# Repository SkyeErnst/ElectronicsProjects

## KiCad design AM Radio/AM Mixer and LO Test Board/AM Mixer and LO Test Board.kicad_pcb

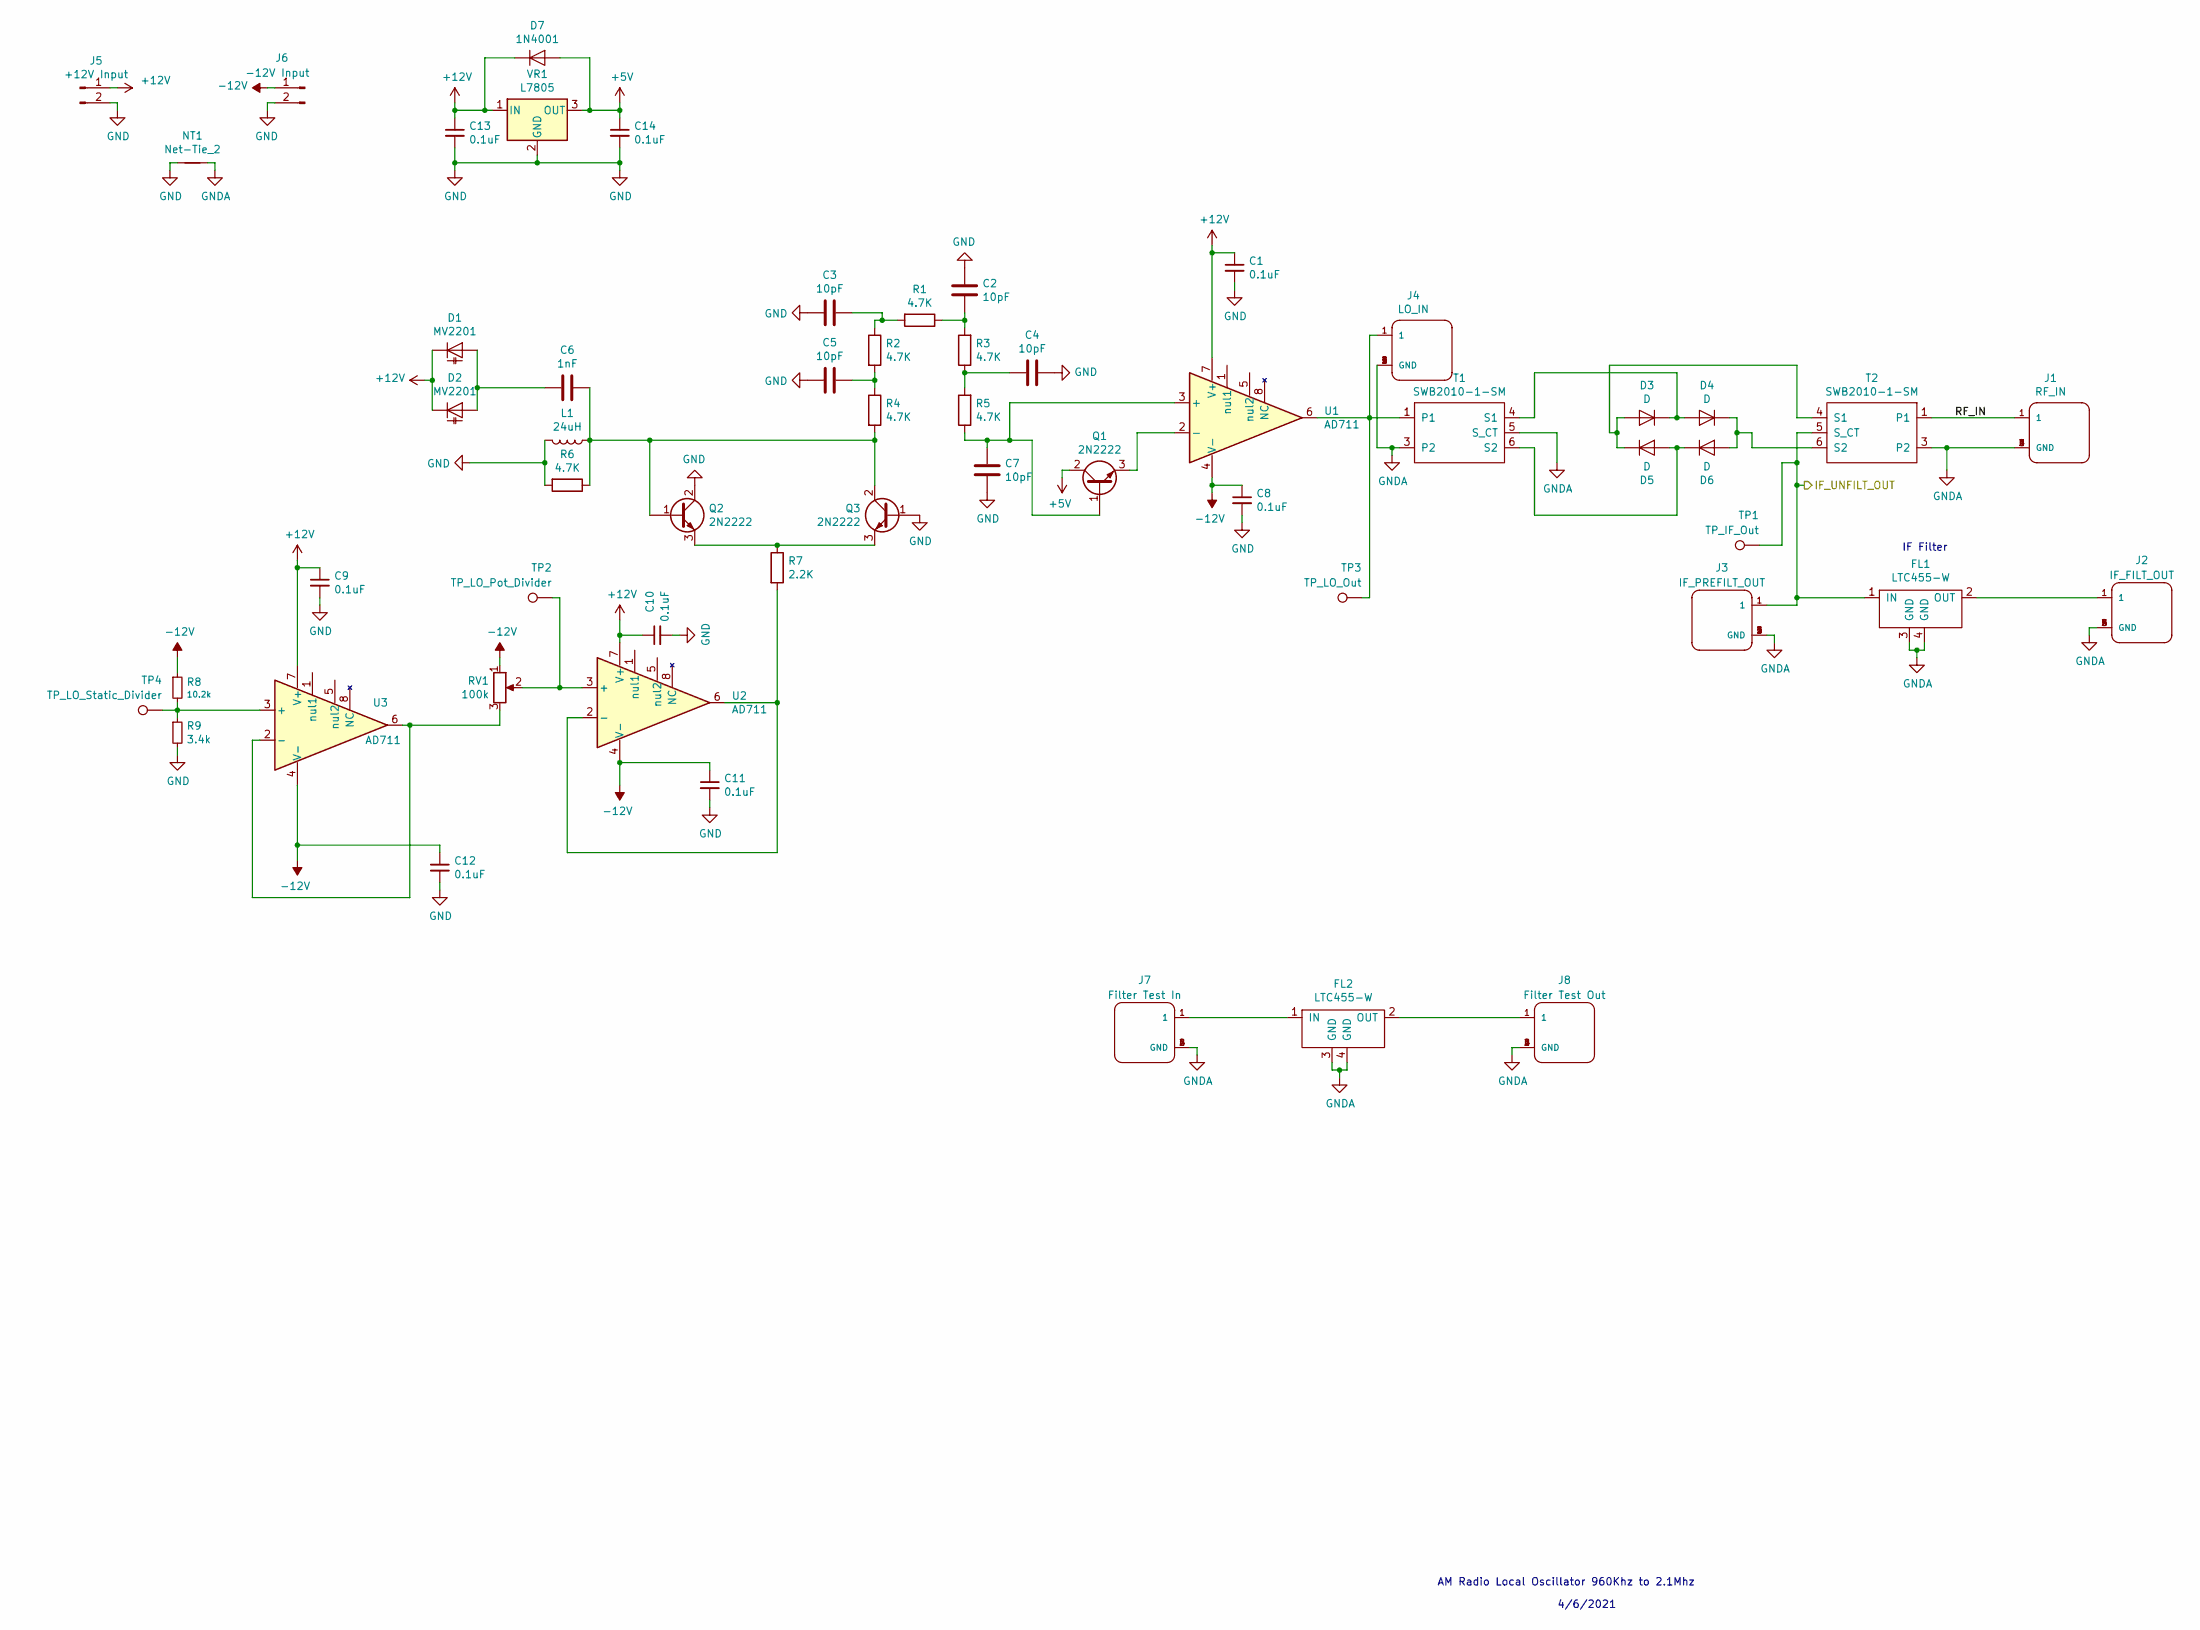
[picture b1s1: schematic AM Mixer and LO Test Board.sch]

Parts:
C1, C8, C9, C10, C11, C12, C13, C14: 0.1uF; C_0805_2012Metric_Pad1.15x1.40mm_HandSolder
C2, C3, C4, C5, C7: 10pF; C_Disc_D3.8mm_W2.6mm_P2.50mm
C6: 1nF; C_Disc_D3.8mm_W2.6mm_P2.50mm
D1, D2: MV2201; C_0402_1005Metric
D3, D4, D5, D6: D; _SC79
D7: 1N4001; D_DO-15_P15.24mm_Horizontal
FL1, FL2: LTC455-W
J1: RF_IN; TE_5-1634503-1
J2: IF_FILT_OUT; TE_5-1634503-1
J3: IF_PREFILT_OUT; TE_5-1634503-1
J4: LO_IN; TE_5-1634503-1
J5: +12V Input; PinHeader_1x02_P2.54mm_Vertical
J6: -12V Input; PinHeader_1x02_P2.54mm_Vertical
J7: Filter Test In; TE_5-1634503-1
J8: Filter Test Out; TE_5-1634503-1
L1: 24uH; L_Axial_L24.0mm_D7.1mm_P30.48mm_Horizontal_Vishay_IM-10-28
NT1: Net-Tie_2; NetTie-2_SMD_Pad0.5mm
Q1, Q2, Q3: 2N2222; TO-92L_HandSolder
R1, R2, R3, R4, R5, R6: 4.7K; R_Axial_DIN0411_L9.9mm_D3.6mm_P15.24mm_Horizontal
R7: 2.2K; R_Axial_DIN0411_L9.9mm_D3.6mm_P15.24mm_Horizontal
R8: 10.2k; R_Axial_DIN0411_L9.9mm_D3.6mm_P15.24mm_Horizontal
R9: 3.4k; R_Axial_DIN0411_L9.9mm_D3.6mm_P15.24mm_Horizontal
RV1: 100k; PinHeader_1x03_P2.54mm_Vertical
T1, T2: SWB2010-1-SM
TP1: TP_IF_Out; TestPoint_Pad_2.5x2.5mm
TP2: TP_LO_Pot_Divider; TestPoint_Pad_2.5x2.5mm
TP3: TP_LO_Out; TestPoint_Pad_2.5x2.5mm
TP4: TP_LO_Static_Divider; TestPoint_Pad_2.5x2.5mm
U1, U2, U3: AD711; DIP-8_W7.62mm_LongPads
VR1: L7805; TO-220-3_Vertical

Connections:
+5V: C14.1, D7.2 (A), Q1.2 (C), VR1.3 (OUT)
+12V: C1.1, C9.1, C10.1, C13.1, D1.1 (K), D2.1 (K), D7.1 (K), J5.1, U1.7 (V+), U2.7 (V+), U3.7 (V+), VR1.1 (IN)
-12V: C8.1, C11.1, C12.1, J6.1, R8.1, RV1.1, U1.4 (V-), U2.4 (V-), U3.4 (V-)
/IF_UNFILT_OUT: FL1.1 (IN), J3.1, T2.5 (S_CT), TP1.1
/RF_IN: J1.1, T2.1
GND: C1.2, C2.1, C3.1, C4.1, C5.1, C7.1, C8.2, C9.2, C10.2, C11.2, C12.2, C13.2, C14.2, J5.2, J6.2, L1.2, NT1.1, Q2.2 (C), Q3.1 (B), R6.2, R9.2, VR1.2 (GND)
GNDA: FL1.3 (GND), FL1.4 (GND), FL2.3 (GND), FL2.4 (GND), J1.2 (GND), J1.3 (GND), J1.4 (GND), J1.5 (GND), J2.2 (GND), J2.3 (GND), J2.4 (GND), J2.5 (GND), J3.2 (GND), J3.3 (GND), J3.4 (GND), J3.5 (GND), J4.2 (GND), J4.3 (GND), J4.4 (GND), J4.5 (GND), J7.2 (GND), J7.3 (GND), J7.4 (GND), J7.5 (GND), J8.2 (GND), J8.3 (GND), J8.4 (GND), J8.5 (GND), NT1.2, T1.3 (P2), T1.5 (S_CT), T2.3 (P2)
unnamed: C2.2, R1.1, R3.2
unnamed: C3.2, R1.2, R2.1
unnamed: C4.2, R3.1, R5.2
unnamed: C5.2, R2.2, R4.1
unnamed: C6.1, L1.1, Q2.1 (B), Q3.2 (C), R4.2, R6.1
unnamed: C6.2, D1.2 (A), D2.2 (A)
unnamed: C7.2, Q1.1 (B), R5.1, U1.3 (+)
unnamed: D3.1 (K), D4.2 (A), T1.4 (S1)
unnamed: D3.2 (A), D5.1 (K), T2.4 (S1)
unnamed: D4.1 (K), D6.2 (A), T2.6 (S2)
unnamed: D5.2 (A), D6.1 (K), T1.6 (S2)
unnamed: FL1.2 (OUT), J2.1
unnamed: FL2.1 (IN), J7.1
unnamed: FL2.2 (OUT), J8.1
unnamed: J4.1, T1.1, TP3.1, U1.6
unnamed: Q1.3 (E), U1.2 (-)
unnamed: Q2.3 (E), Q3.3 (E), R7.1
unnamed: R7.2, U2.2 (-), U2.6
unnamed: R8.2, R9.1, TP4.1, U3.3 (+)
unnamed: RV1.2, TP2.1, U2.3 (+)
unnamed: RV1.3, U3.2 (-), U3.6

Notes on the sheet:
AM Radio Local Oscillator 960Khz to 2.1Mhz
4/6/2021
IF Filter

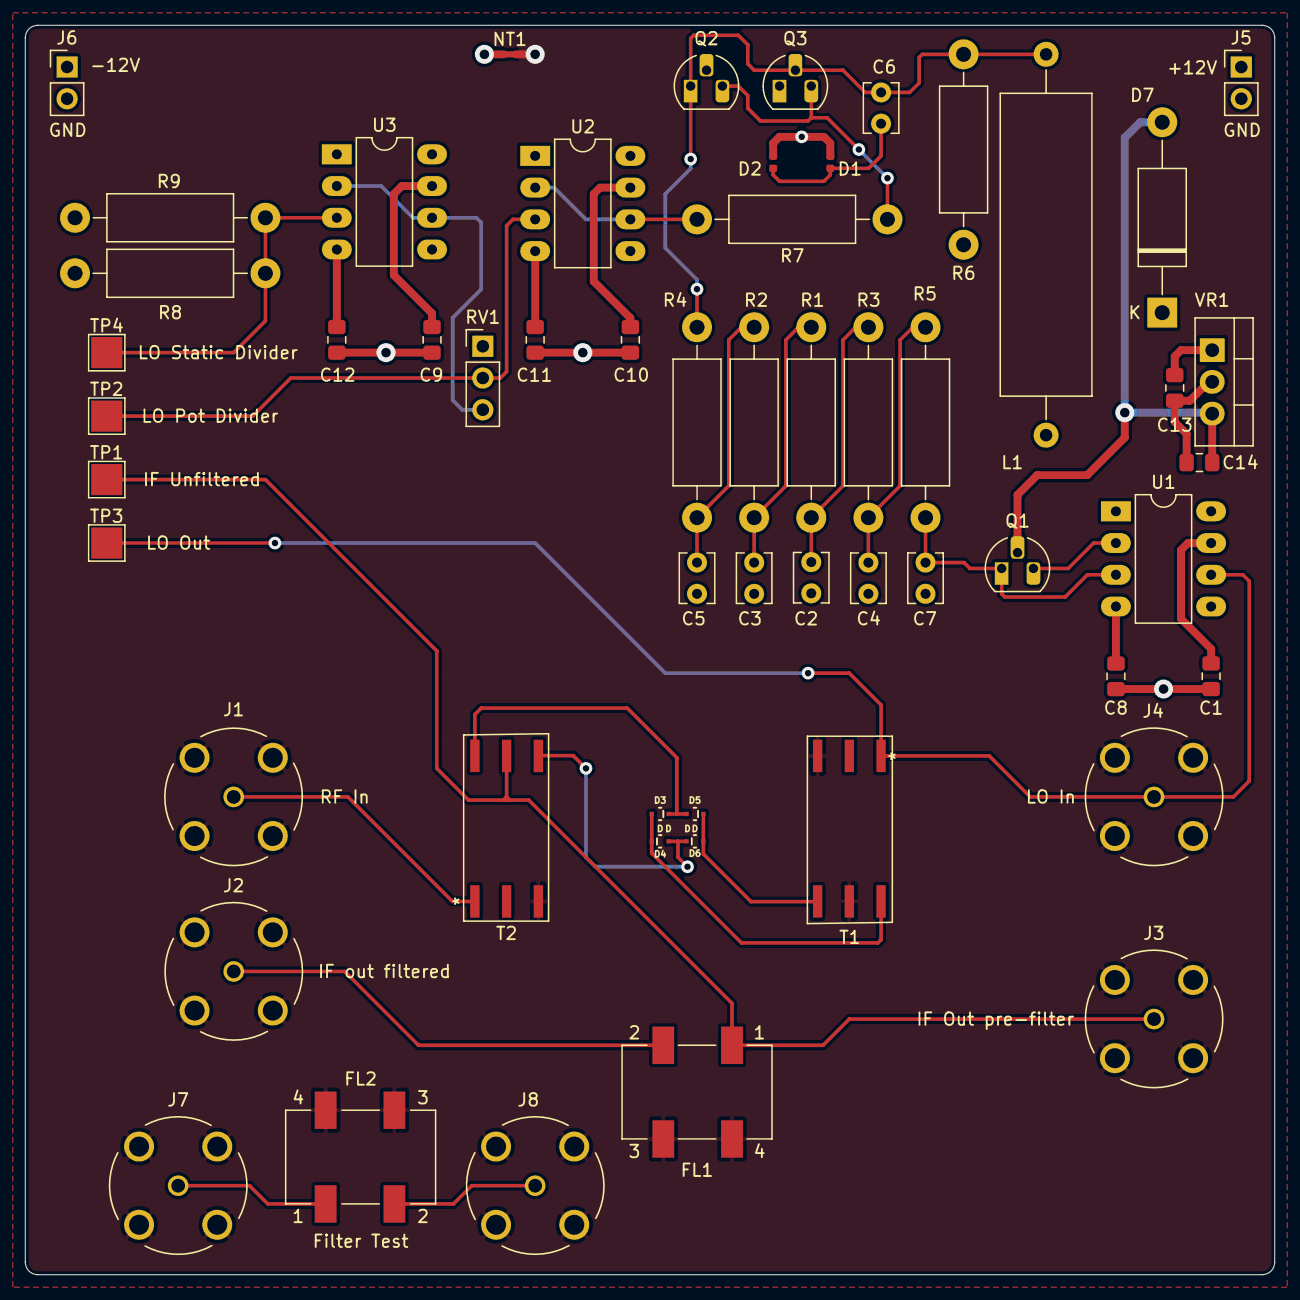
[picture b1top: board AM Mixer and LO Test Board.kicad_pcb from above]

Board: 4 copper layers, 100.0 x 100.0 mm, 56 parts (0 on the bottom side), 28 nets.

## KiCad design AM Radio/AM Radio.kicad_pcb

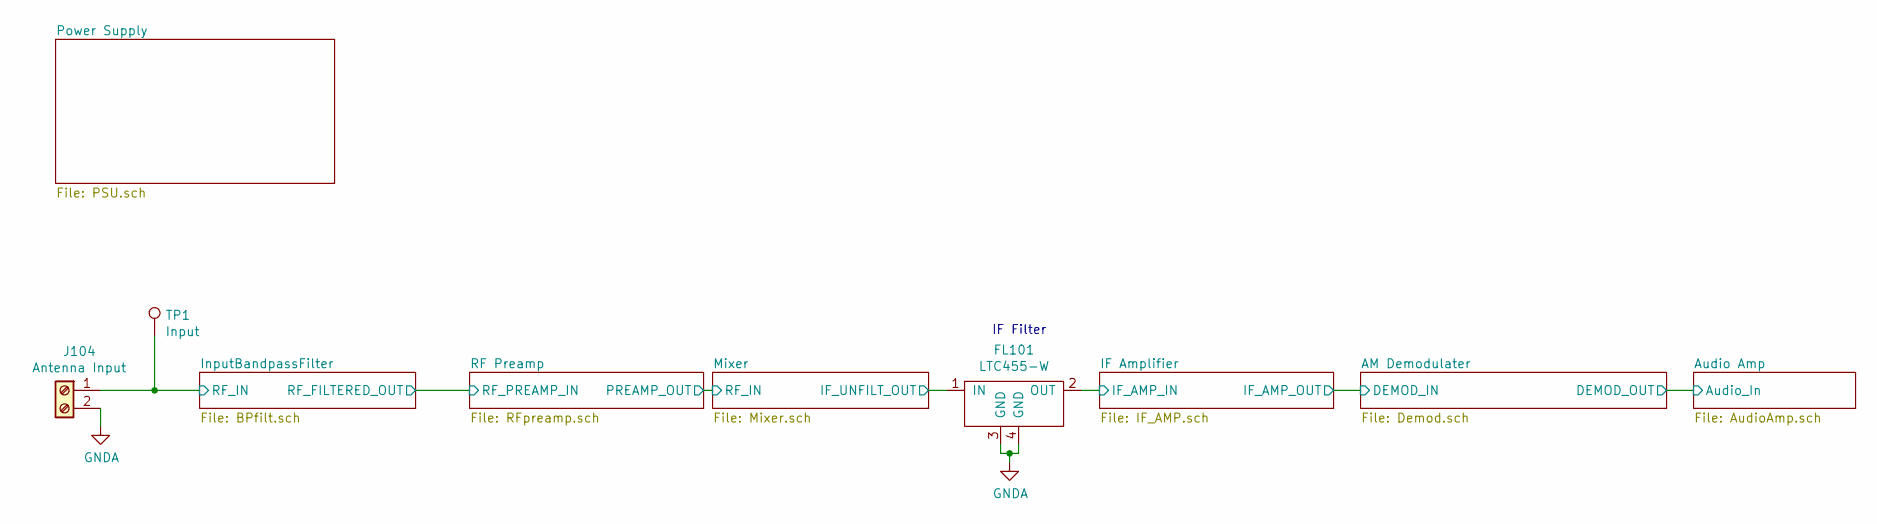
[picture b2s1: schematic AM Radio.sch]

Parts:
FL101: LTC455-W
J104: Antenna Input; Altech_AK300_1x02_P5.00mm_45-Degree
TP1: Input; TestPoint_Pad_2.5x2.5mm

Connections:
/IF Amplifier/IF_AMP_IN: FL101.2 (OUT); also elsewhere on the board
/InputBandpassFilter/RF_IN: J104.1, TP1.1; also elsewhere on the board
/Mixer/IF_UNFILT_OUT: FL101.1 (IN); also elsewhere on the board
GNDA: FL101.3 (GND), FL101.4 (GND), J104.2; also elsewhere on the board

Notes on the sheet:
IF Filter

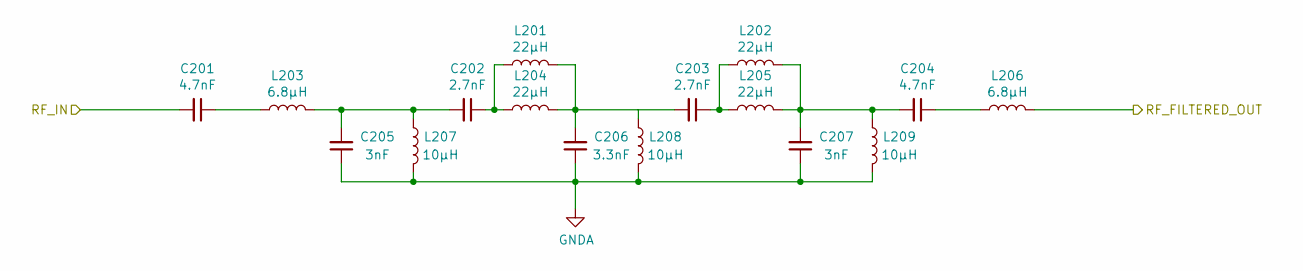
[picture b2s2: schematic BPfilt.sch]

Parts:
C201, C204: 4.7nF; C_0805_2012Metric_Pad1.15x1.40mm_HandSolder
C202, C203: 2.7nF; C_0805_2012Metric_Pad1.15x1.40mm_HandSolder
C205, C207: 3nF; C_0805_2012Metric_Pad1.15x1.40mm_HandSolder
C206: 3.3nF; C_0805_2012Metric_Pad1.15x1.40mm_HandSolder
L201, L202, L204, L205: 22µH; L_0805_2012Metric_Pad1.15x1.40mm_HandSolder
L203, L206: 6.8µH; L_0805_2012Metric_Pad1.15x1.40mm_HandSolder
L207, L208, L209: 10µH; L_0805_2012Metric_Pad1.15x1.40mm_HandSolder

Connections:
/InputBandpassFilter/RF_FILTERED_OUT: L206.2; also elsewhere on the board
/InputBandpassFilter/RF_IN: C201.2; also elsewhere on the board
GNDA: C205.1, C206.1, C207.1, L207.2, L208.2, L209.2; also elsewhere on the board
unnamed: C201.1, L203.1
unnamed: C202.1, L201.1, L204.1
unnamed: C202.2, C205.2, L203.2, L207.1
unnamed: C203.1, L202.1, L205.1
unnamed: C203.2, C206.2, L201.2, L204.2, L208.1
unnamed: C204.1, L206.1
unnamed: C204.2, C207.2, L202.2, L205.2, L209.1

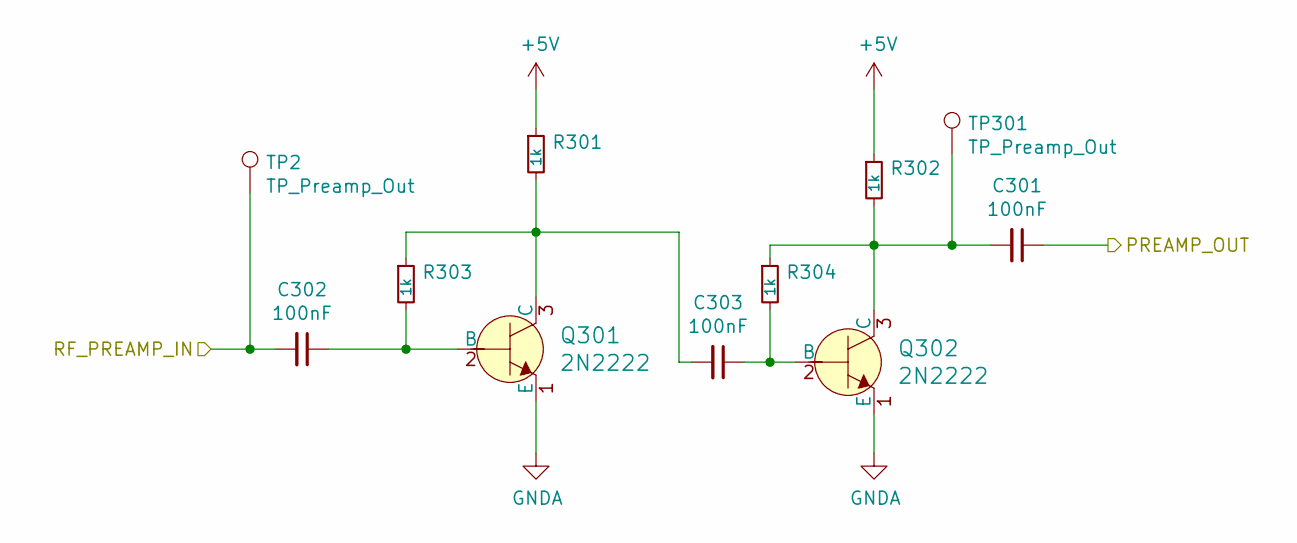
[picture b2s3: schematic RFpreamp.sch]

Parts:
C301, C302, C303: 100nF; C_0805_2012Metric_Pad1.15x1.40mm_HandSolder
Q301, Q302: 2N2222; SOT-23
R301, R302, R303, R304: 1k; R_0805_2012Metric_Pad1.15x1.40mm_HandSolder
TP2, TP301: TP_Preamp_Out; TestPoint_Pad_2.5x2.5mm

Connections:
+5V: R301.1, R302.1; also elsewhere on the board
/InputBandpassFilter/RF_FILTERED_OUT: C302.2, TP2.1; also elsewhere on the board
/RF Preamp/PREAMP_OUT: C301.1; also elsewhere on the board
GNDA: Q301.1 (E), Q302.1 (E); also elsewhere on the board
unnamed: C301.2, Q302.3 (C), R302.2, R304.1, TP301.1
unnamed: C302.1, Q301.2 (B), R303.2
unnamed: C303.1, Q302.2 (B), R304.2
unnamed: C303.2, Q301.3 (C), R301.2, R303.1

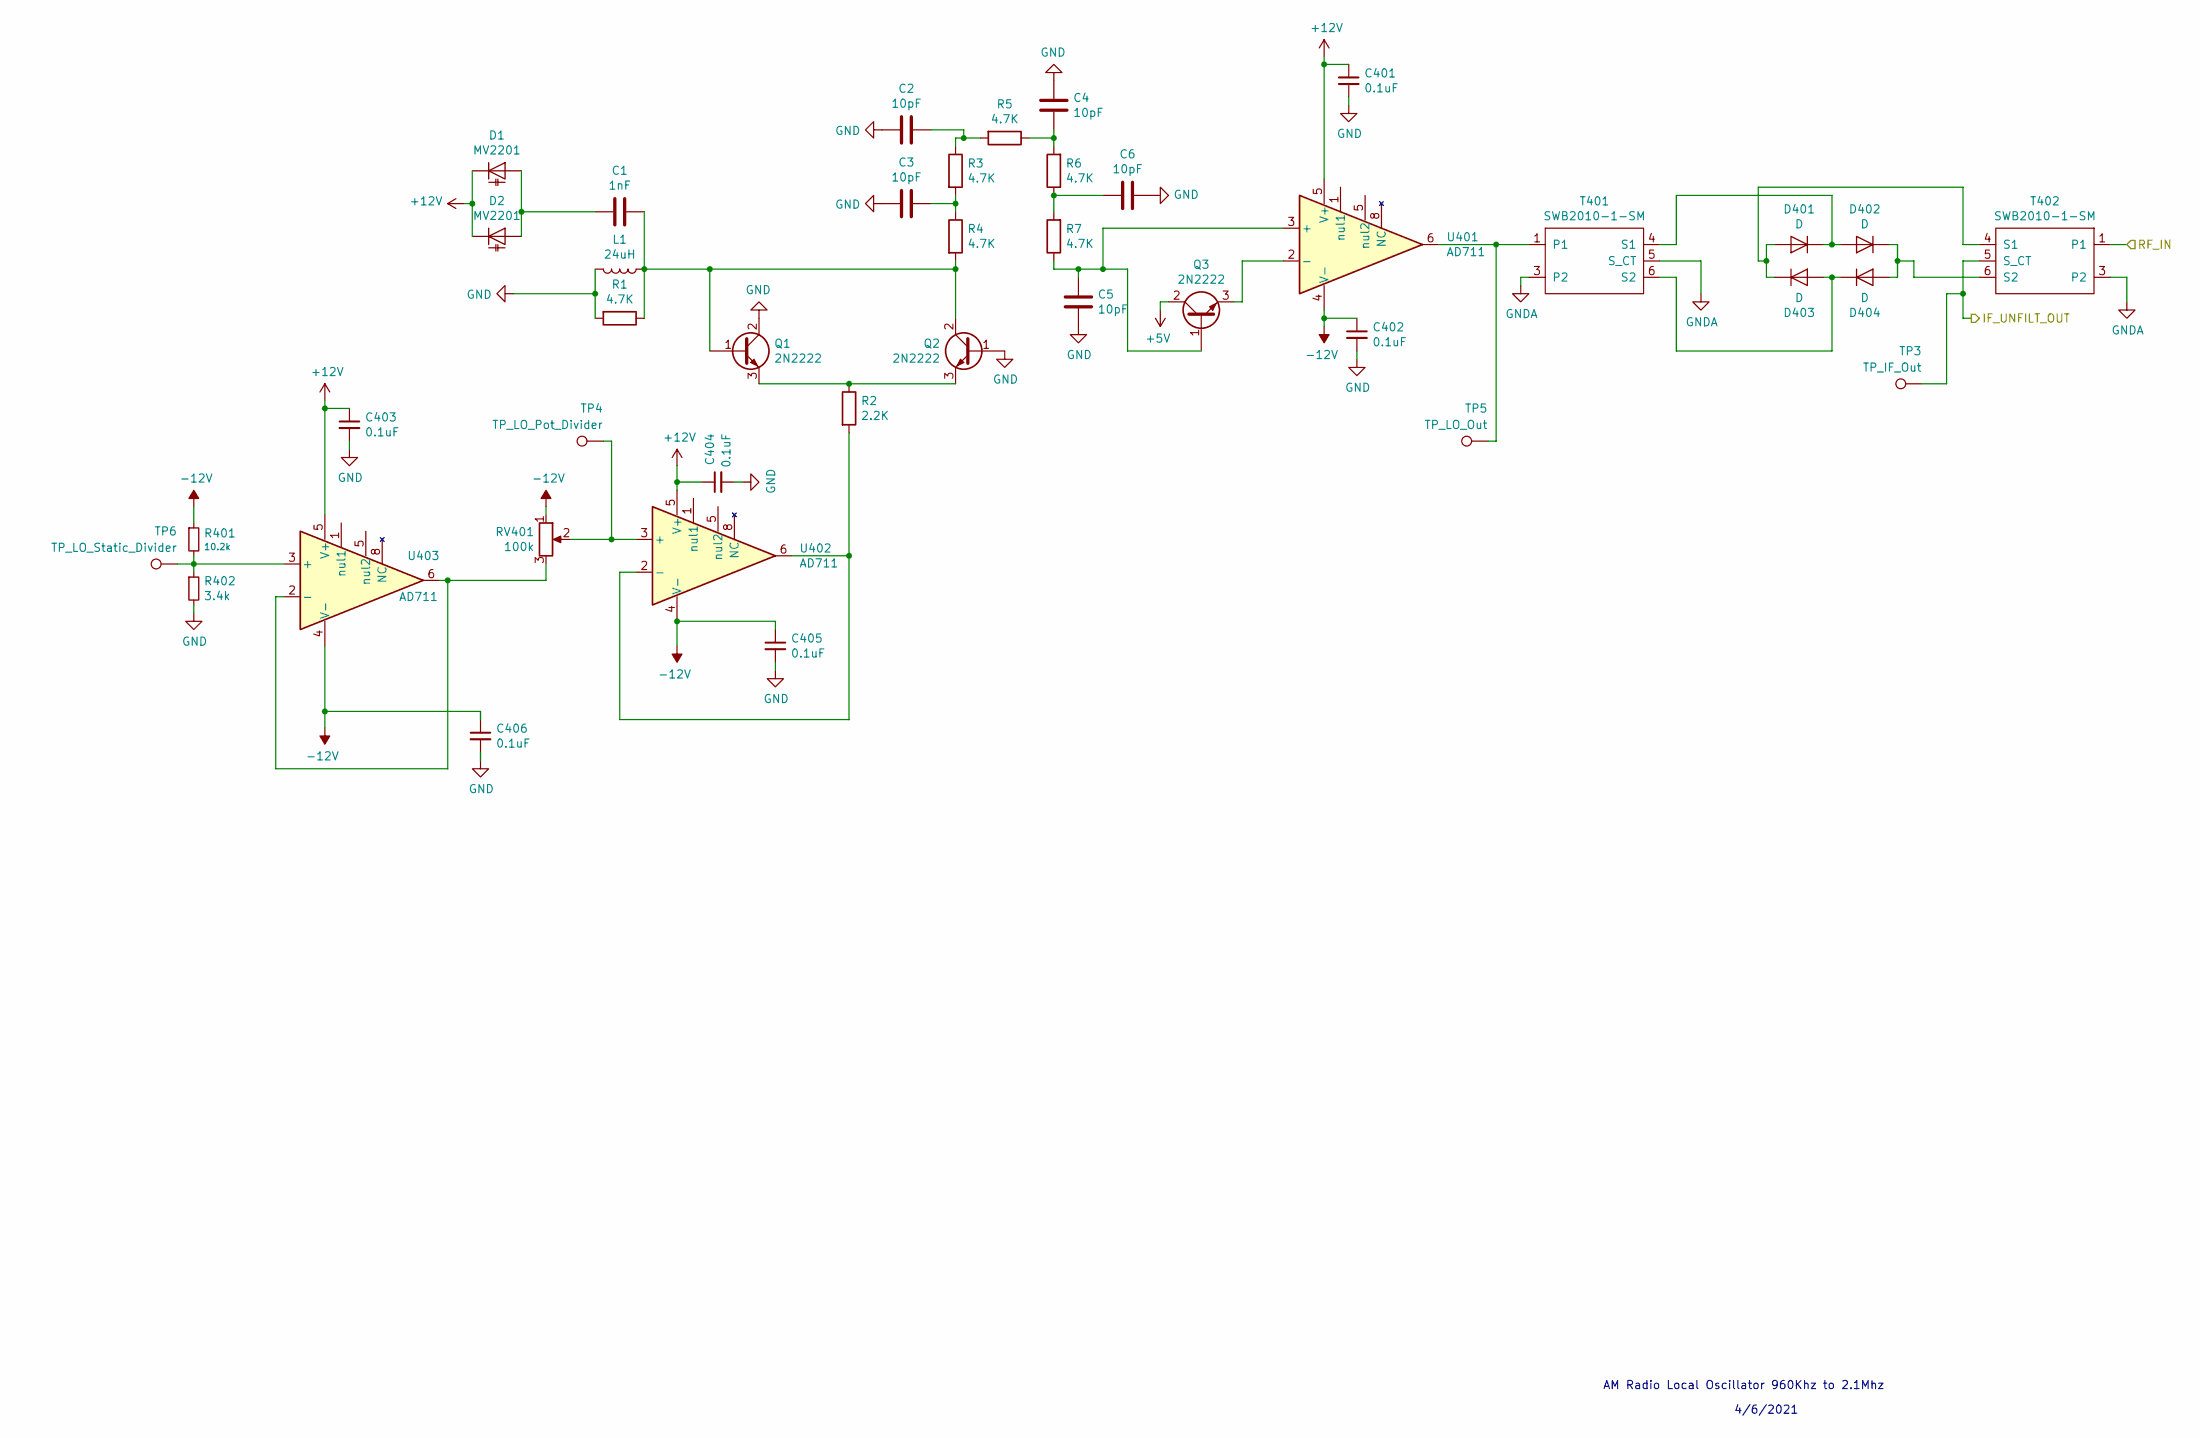
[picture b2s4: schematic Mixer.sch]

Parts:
C1: 1nF; C_0805_2012Metric_Pad1.15x1.40mm_HandSolder
C2, C3, C4, C5, C6: 10pF; C_0805_2012Metric_Pad1.15x1.40mm_HandSolder
C401, C402, C403, C404, C405, C406: 0.1uF; C_0805_2012Metric_Pad1.15x1.40mm_HandSolder
D1, D2: MV2201; C_0402_1005Metric
D401, D402, D403, D404: D; D_0805_2012Metric_Pad1.15x1.40mm_HandSolder
L1: 24uH; L_0805_2012Metric_Pad1.15x1.40mm_HandSolder
Q1, Q2, Q3: 2N2222; SOT-23
R1, R3, R4, R5, R6, R7: 4.7K; R_0805_2012Metric_Pad1.15x1.40mm_HandSolder
R2: 2.2K; R_0805_2012Metric_Pad1.15x1.40mm_HandSolder
R401: 10.2k; R_0805_2012Metric_Pad1.15x1.40mm_HandSolder
R402: 3.4k; R_0805_2012Metric_Pad1.15x1.40mm_HandSolder
RV401: 100k; Potentiometer_Bourns_3266W_Vertical
T401, T402: SWB2010-1-SM
TP3: TP_IF_Out; TestPoint_Pad_2.5x2.5mm
TP4: TP_LO_Pot_Divider; TestPoint_Pad_2.5x2.5mm
TP5: TP_LO_Out; TestPoint_Pad_2.5x2.5mm
TP6: TP_LO_Static_Divider; TestPoint_Pad_2.5x2.5mm
U401, U402, U403: AD711; DIP-8_W7.62mm_LongPads

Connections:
+5V: Q3.2 (C); also elsewhere on the board
+12V: C401.1, C403.1, C404.1, D1.1 (K), D2.1 (K), U401.5 (nul2), U402.5 (nul2), U403.5 (nul2); also elsewhere on the board
-12V: C402.1, C405.1, C406.1, R401.1, RV401.1, U401.4 (V-), U402.4 (V-), U403.4 (V-); also elsewhere on the board
/Mixer/IF_UNFILT_OUT: T402.5 (S_CT), TP3.1; also elsewhere on the board
/RF Preamp/PREAMP_OUT: T402.1; also elsewhere on the board
GND: C2.1, C3.1, C4.1, C5.1, C6.1, C401.2, C402.2, C403.2, C404.2, C405.2, C406.2, L1.2, Q1.2 (C), Q2.1 (B), R1.2, R402.2; also elsewhere on the board
GNDA: T401.3 (P2), T401.5 (S_CT), T402.3 (P2); also elsewhere on the board
unnamed: C1.1, L1.1, Q1.1 (B), Q2.2 (C), R1.1, R4.2
unnamed: C1.2, D1.2 (A), D2.2 (A)
unnamed: C2.2, R3.1, R5.2
unnamed: C3.2, R3.2, R4.1
unnamed: C4.2, R5.1, R6.2
unnamed: C5.2, Q3.1 (B), R7.1, U401.3 (+)
unnamed: C6.2, R6.1, R7.2
unnamed: D401.1 (K), D402.2 (A), T401.4 (S1)
unnamed: D401.2 (A), D403.1 (K), T402.4 (S1)
unnamed: D402.1 (K), D404.2 (A), T402.6 (S2)
unnamed: D403.2 (A), D404.1 (K), T401.6 (S2)
unnamed: Q1.3 (E), Q2.3 (E), R2.1
unnamed: Q3.3 (E), U401.2 (-)
unnamed: R2.2, U402.2 (-), U402.6
unnamed: R401.2, R402.1, TP6.1, U403.3 (+)
unnamed: RV401.2, TP4.1, U402.3 (+)
unnamed: RV401.3, U403.2 (-), U403.6
unnamed: T401.1, TP5.1, U401.6

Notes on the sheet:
AM Radio Local Oscillator 960Khz to 2.1Mhz
4/6/2021

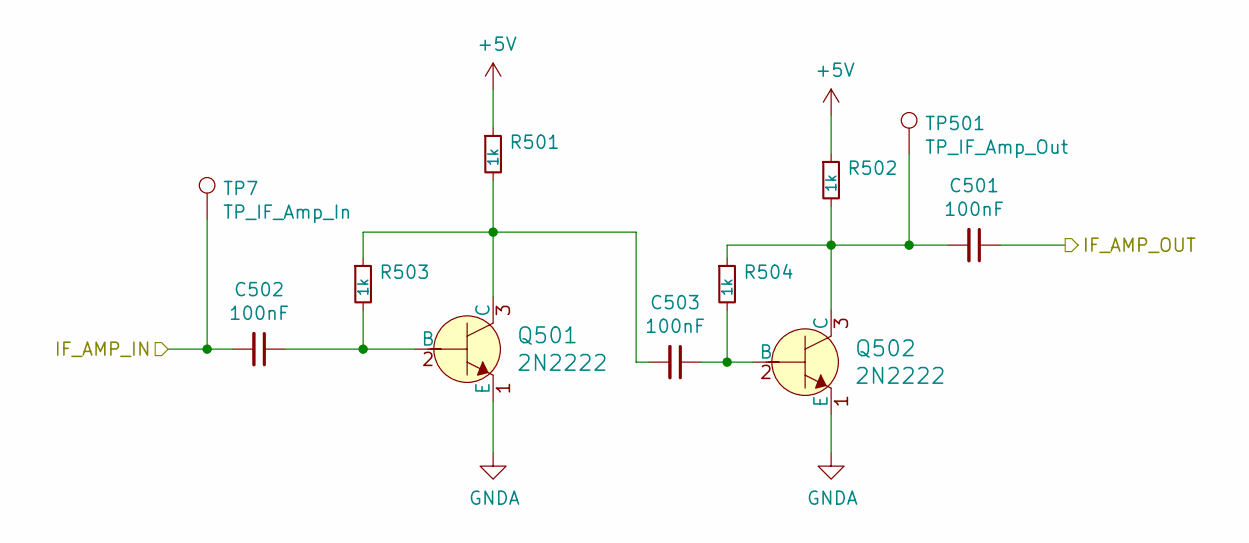
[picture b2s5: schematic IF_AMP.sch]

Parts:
C501, C502, C503: 100nF; C_0805_2012Metric_Pad1.15x1.40mm_HandSolder
Q501, Q502: 2N2222; SOT-23
R501, R502, R503, R504: 1k; R_0805_2012Metric_Pad1.15x1.40mm_HandSolder
TP7: TP_IF_Amp_In; TestPoint_Pad_2.5x2.5mm
TP501: TP_IF_Amp_Out; TestPoint_Pad_2.5x2.5mm

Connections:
+5V: R501.1, R502.1; also elsewhere on the board
/AM Demodulater/DEMOD_IN: C501.1; also elsewhere on the board
/IF Amplifier/IF_AMP_IN: C502.2, TP7.1; also elsewhere on the board
GNDA: Q501.1 (E), Q502.1 (E); also elsewhere on the board
unnamed: C501.2, Q502.3 (C), R502.2, R504.1, TP501.1
unnamed: C502.1, Q501.2 (B), R503.2
unnamed: C503.1, Q502.2 (B), R504.2
unnamed: C503.2, Q501.3 (C), R501.2, R503.1

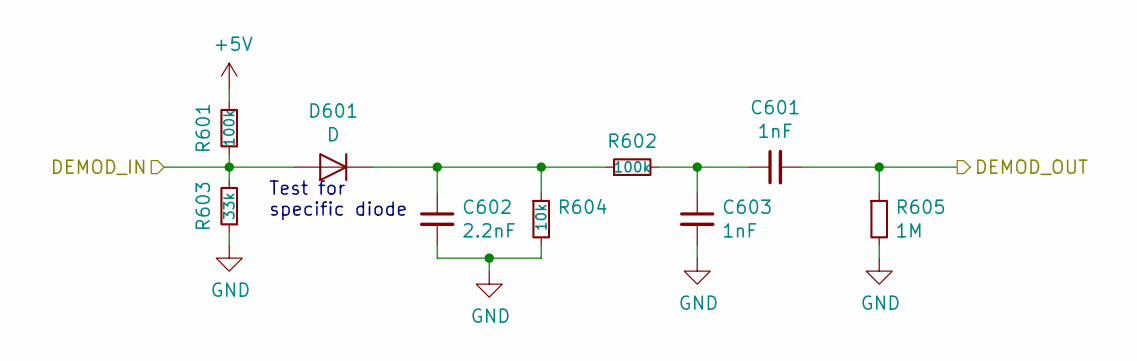
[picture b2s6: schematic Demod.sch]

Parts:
C601, C603: 1nF; C_0805_2012Metric_Pad1.15x1.40mm_HandSolder
C602: 2.2nF; C_0805_2012Metric_Pad1.15x1.40mm_HandSolder
D601: D; D_0805_2012Metric_Pad1.15x1.40mm_HandSolder
R601, R602: 100k; R_0805_2012Metric_Pad1.15x1.40mm_HandSolder
R603: 33k; R_0805_2012Metric_Pad1.15x1.40mm_HandSolder
R604: 10k; R_0805_2012Metric_Pad1.15x1.40mm_HandSolder
R605: 1M; R_0805_2012Metric_Pad1.15x1.40mm_HandSolder

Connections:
+5V: R601.2; also elsewhere on the board
/AM Demodulater/DEMOD_IN: D601.2 (A), R601.1, R603.2; also elsewhere on the board
/Audio Amp/Audio_In: C601.2, R605.1; also elsewhere on the board
GND: C602.2, C603.2, R603.1, R604.2, R605.2; also elsewhere on the board
unnamed: C601.1, C603.1, R602.2
unnamed: C602.1, D601.1 (K), R602.1, R604.1

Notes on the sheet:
Test for specific diode

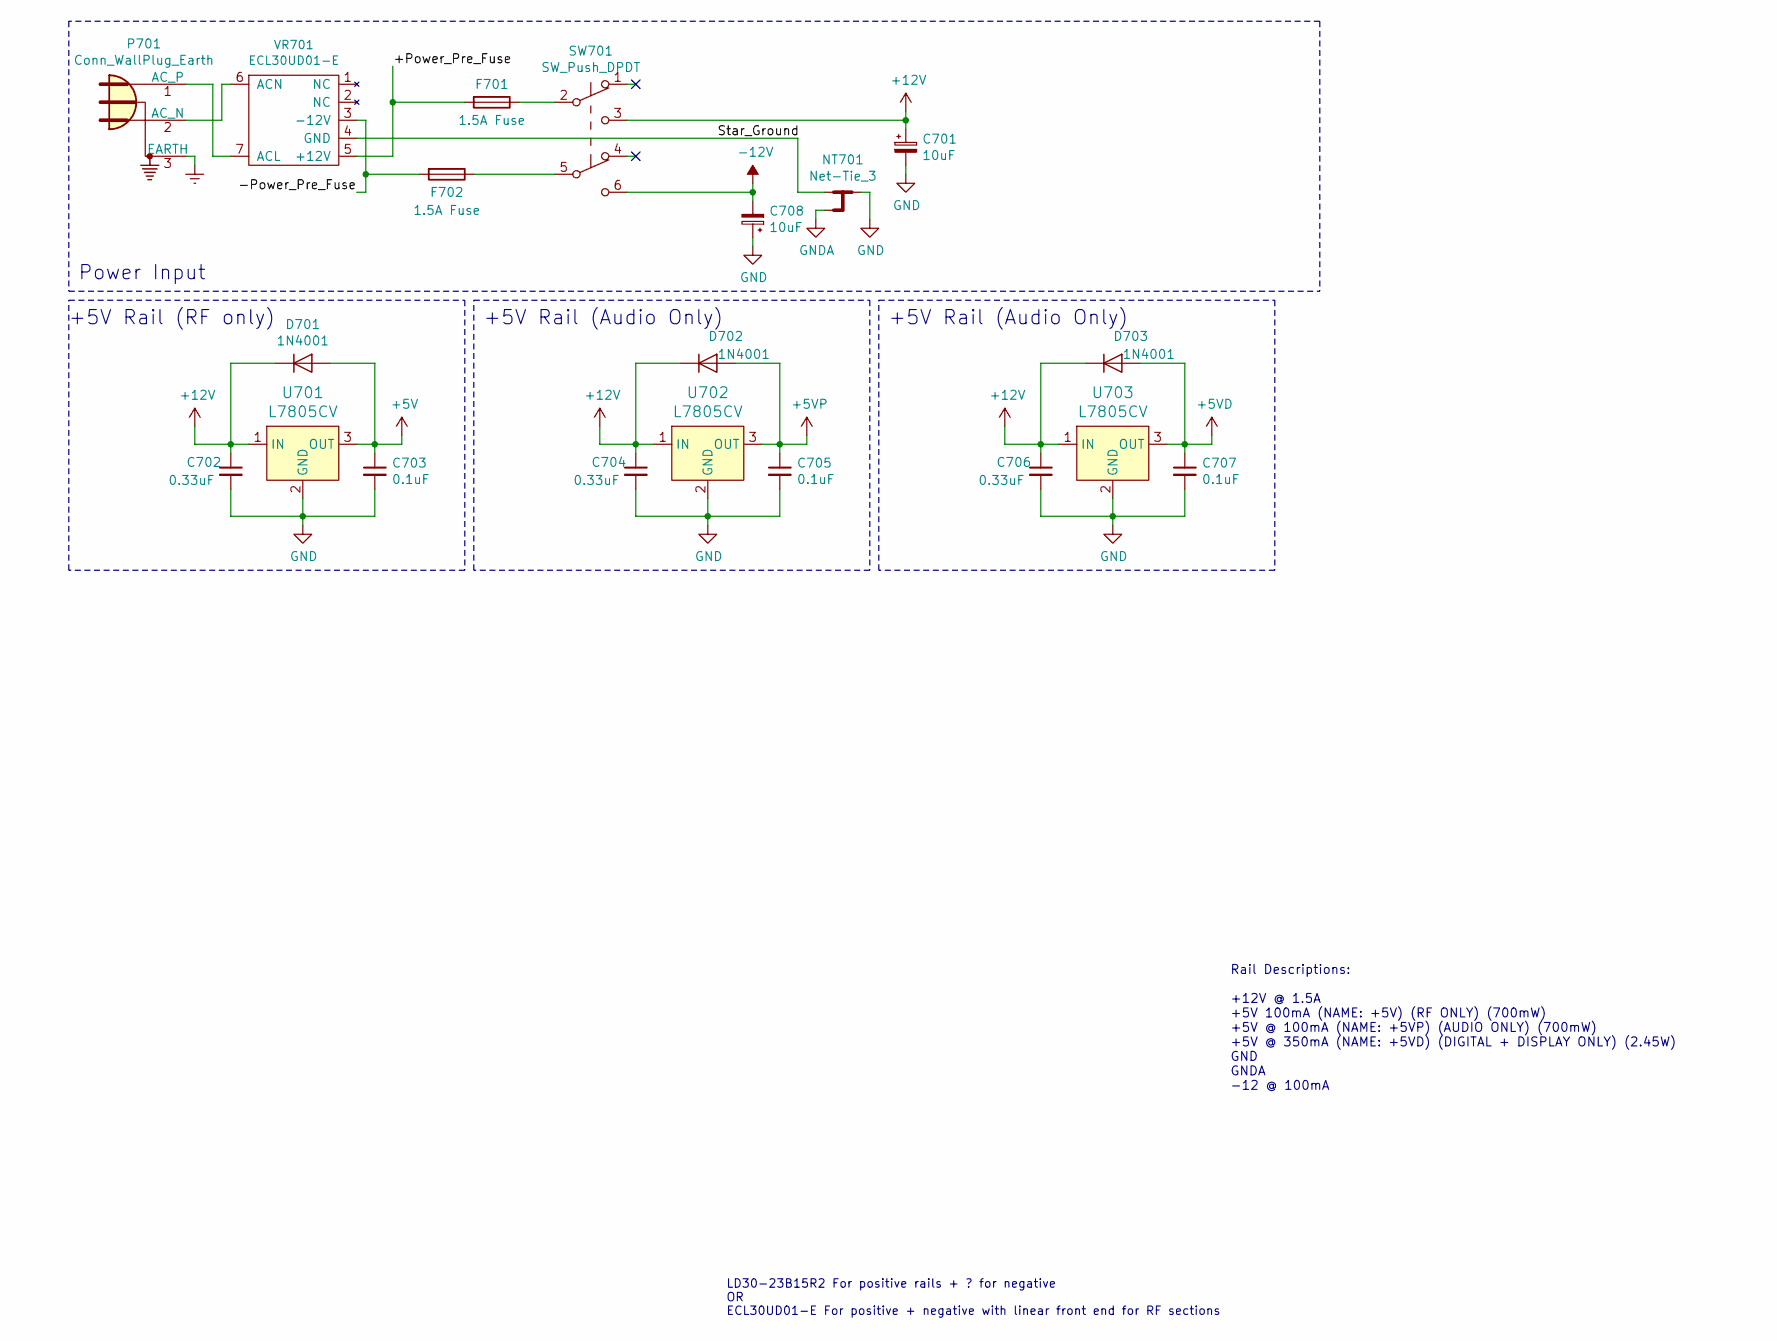
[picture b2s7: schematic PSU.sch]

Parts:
C701, C708: 10uF; CP_Radial_D5.0mm_P2.50mm
C702, C704, C706: 0.33uF; C_0805_2012Metric_Pad1.15x1.40mm_HandSolder
C703, C705, C707: 0.1uF; C_0805_2012Metric_Pad1.15x1.40mm_HandSolder
D701, D702, D703: 1N4001; D_0805_2012Metric_Pad1.15x1.40mm_HandSolder
F701, F702: 1.5A Fuse; Fuse_0805_2012Metric_Pad1.15x1.40mm_HandSolder
NT701: Net-Tie_3; NetTie-3_SMD_Pad2.0mm
P701: Conn_WallPlug_Earth; Diodes_SIP-3_4.1x1.5mm_P2.65mm
SW701: SW_Push_DPDT; PinSocket_1x06_P2.54mm_Vertical
U701, U702, U703: L7805CV; TO-220-3_Vertical; MPN L7805CV; Digi-Key_PN 497-1443-5-ND
VR701: ECL30UD01-E

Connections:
+5V: C703.1, D701.2 (A), U701.3 (OUT); also elsewhere on the board
+5VD: C707.1, D703.2 (A), U703.3 (OUT)
+5VP: C705.1, D702.2 (A), U702.3 (OUT); also elsewhere on the board
+12V: C701.1, C702.1, C704.1, C706.1, D701.1 (K), D702.1 (K), D703.1 (K), SW701.3 (C), U701.1 (IN), U702.1 (IN), U703.1 (IN); also elsewhere on the board
-12V: C708.2, SW701.6 (C); also elsewhere on the board
/Power Supply/+Power_Pre_Fuse: F701.2, VR701.5 (+12V)
/Power Supply/-Power_Pre_Fuse: F702.2, VR701.3 (-12V)
/Power Supply/Star_Ground: NT701.1, VR701.4 (GND)
Earth: P701.3 (EARTH)
GND: C701.2, C702.2, C703.2, C704.2, C705.2, C706.2, C707.2, C708.1, NT701.2, U701.2 (GND), U702.2 (GND), U703.2 (GND); also elsewhere on the board
GNDA: NT701.3; also elsewhere on the board
unnamed: F701.1, SW701.2 (B)
unnamed: F702.1, SW701.5 (B)
unnamed: P701.1 (AC_P), VR701.7 (ACL)
unnamed: P701.2 (AC_N), VR701.6 (ACN)

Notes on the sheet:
Power Input
+5V Rail (RF only)
+5V Rail (Audio Only)
LD30-23B15R2 For positive rails + ? for negative OR ECL30UD01-E For positive + negative with linear front end for RF sections
Rail Descriptions: +12V @ 1.5A +5V 100mA (NAME: +5V) (RF ONLY) (700mW) +5V @ 100mA (NAME: +5VP) (AUDIO ONLY) (700mW) +5V @ 350mA (NAME: +5VD) (DIGITAL + DISPLAY ONLY) (2.45W) GND GNDA -12 @ 100mA

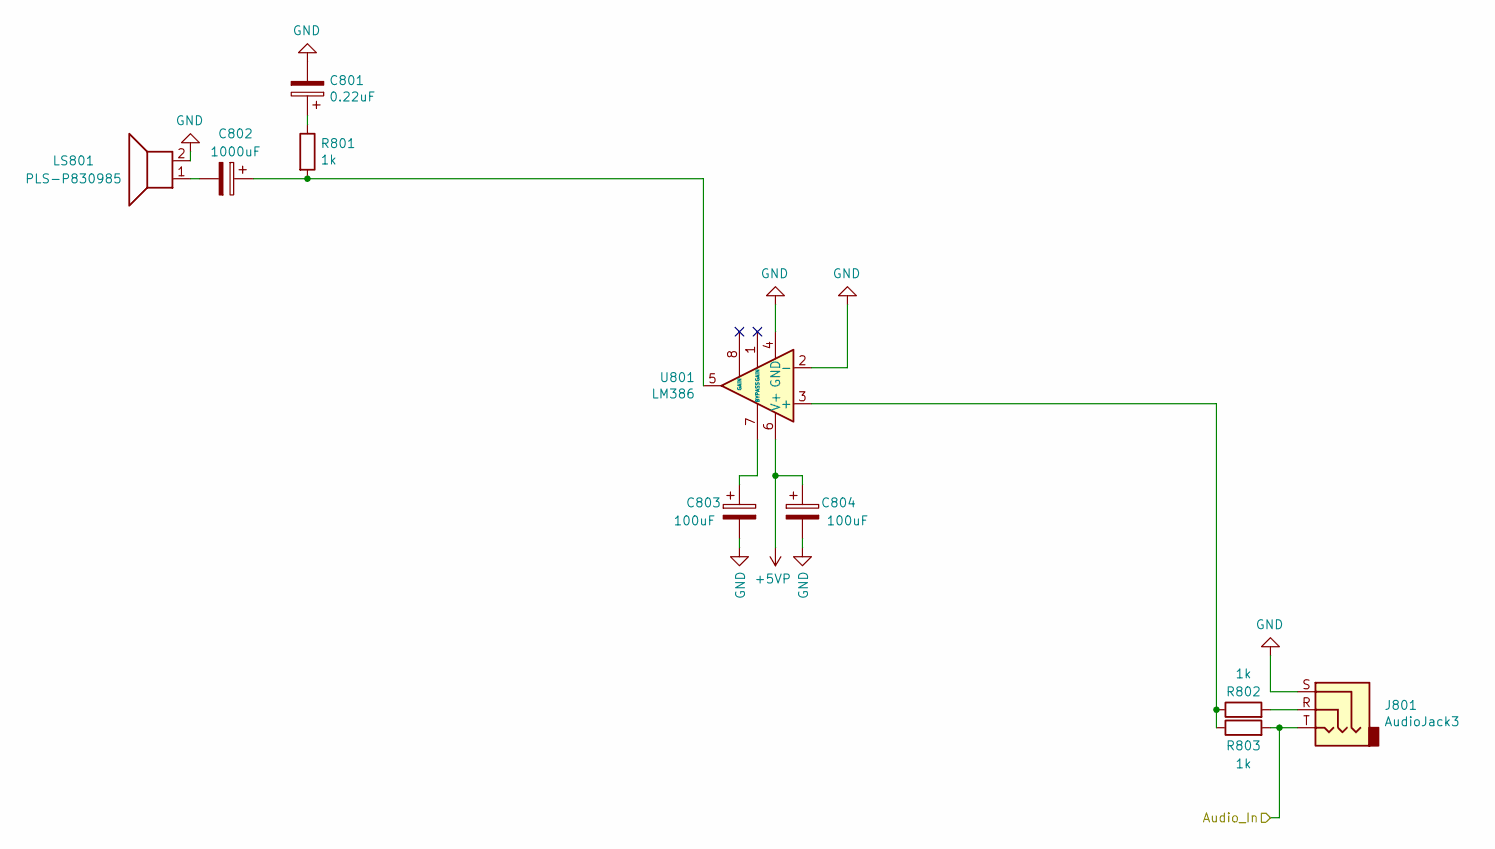
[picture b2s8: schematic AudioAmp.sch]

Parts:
C801: 0.22uF; CP_Radial_D5.0mm_P2.50mm
C802: 1000uF; CP_Radial_D10.0mm_P5.00mm
C803, C804: 100uF; CP_Radial_D5.0mm_P2.50mm
J801: AudioJack3; Jack_3.5mm_Switronic_ST-005-G_horizontal
LS801: PLS-P830985; PinSocket_1x02_P2.54mm_Vertical
R801, R802, R803: 1k; R_Axial_DIN0207_L6.3mm_D2.5mm_P10.16mm_Horizontal
U801: LM386; DIP-8_W7.62mm

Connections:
+5VP: C804.1, U801.6 (V+); also elsewhere on the board
/Audio Amp/Audio_In: J801.T, R803.2; also elsewhere on the board
GND: C801.2, C803.2, C804.2, J801.S, LS801.2, U801.2 (-), U801.4 (GND); also elsewhere on the board
unnamed: C801.1, R801.1
unnamed: C802.1, R801.2, U801.5
unnamed: C802.2, LS801.1
unnamed: C803.1, U801.7 (BYPASS)
unnamed: J801.R, R802.2
unnamed: R802.1, R803.1, U801.3 (+)

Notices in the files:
parts and their libraries:
Copyright 2016 Accelerated Designs. All rights reserved.
